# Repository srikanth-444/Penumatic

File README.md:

# _Peumatic Backpack_
This is a Penumatic System that senses and actuates the multiple soft actuators while communicating with the remote pc 

## _Hardware_ 
To control and sense the robotic actuator system, developed using KiCad 8, this repository will build the Gerber files of the system upon pushing the action artifacts specific to JLCPCB 

| Component     | Function            | Notes                                                    |
| ------------- | ------------------- | -------------------------------------------------------- |
| **ESP-32 S3** | Microcontroller     | Handles system control, communication, and overall logic |
| **LTC2498**   | 24-bit ADC          | Senses actuator position with high precision             |
| **LTC6906**   | External oscillator | Provides clock signal for ADC operation                  |
| **MCZ33996**  | Solenoid driver     | Actuates solenoidal valves based on control signals      |

## _Firmware_ 
Developed in C using FreeRTOS for increased concurrency. Code is developed using VSCode ESP-IDF extension

### Images

rendered with [kicad-render](https://github.com/linalinn/kicad-render)

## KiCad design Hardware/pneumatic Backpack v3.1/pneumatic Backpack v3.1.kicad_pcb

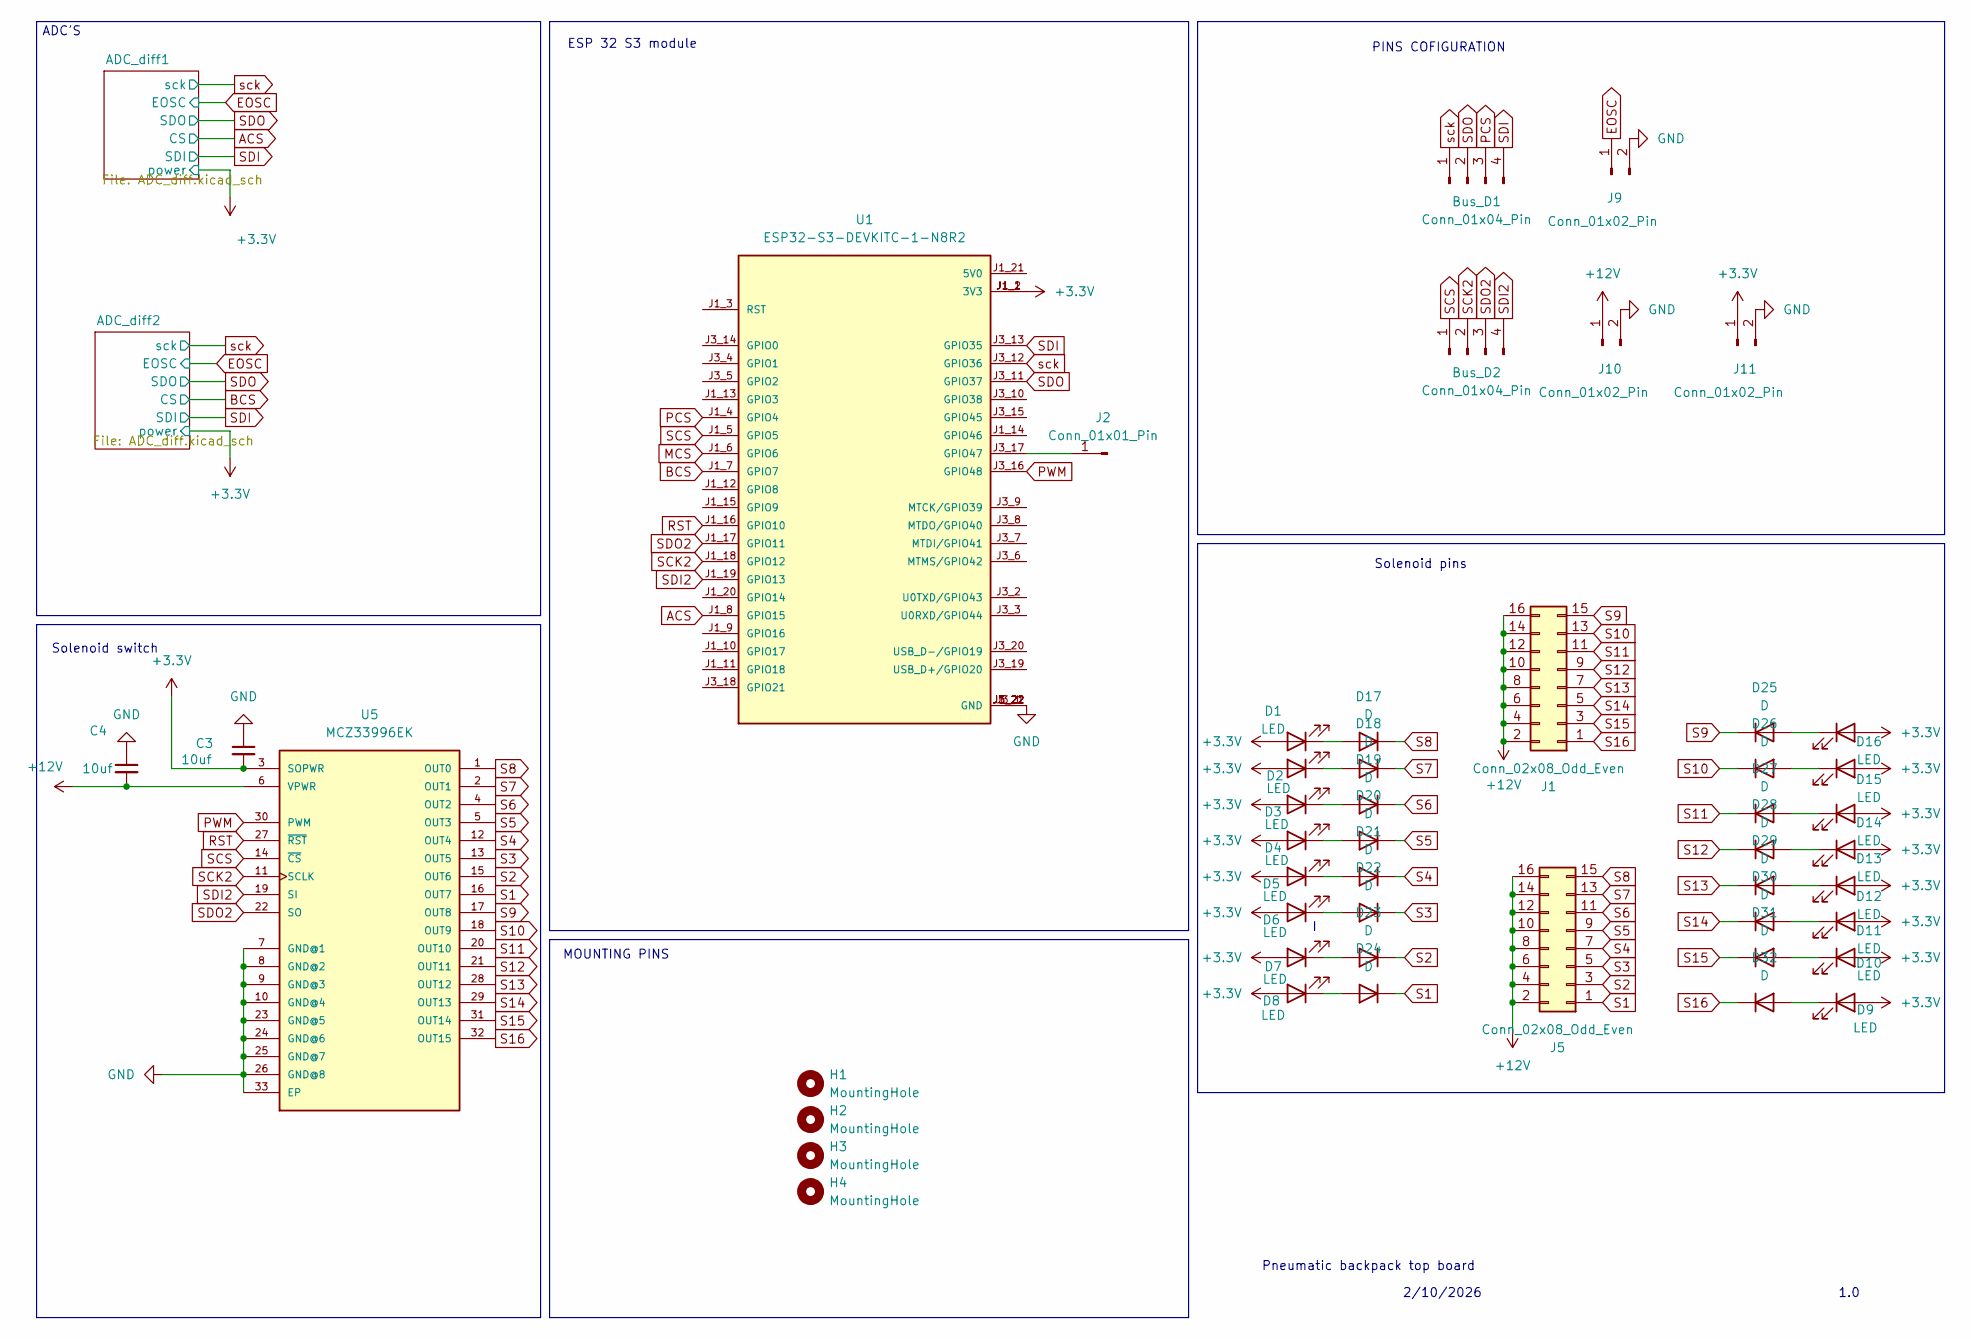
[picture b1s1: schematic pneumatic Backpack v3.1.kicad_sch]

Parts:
Bus_D1: Conn_01x04_Pin; PinSocket_1x04_P2.54mm_Vertical
Bus_D2: Conn_01x04_Pin; PinSocket_1x04_P2.54mm_Horizontal
C3, C4: 10uf; C_1206_3216Metric_Pad1.33x1.80mm_HandSolder
D1, D2, D3, D4, D5, D6, D7, D8, D9, D10, D11, D12, D13, D14, D15, D16: LED; LED_0805_2012Metric_Pad1.15x1.40mm_HandSolder
D17, D18, D19, D20, D21, D22, D23, D24, D25, D26, D27, D28, D29, D30, D31, D32: D; D_0805_2012Metric_Pad1.15x1.40mm_HandSolder
H1, H2, H3, H4: MountingHole; MountingHole_2.5mm
J1, J5: Conn_02x08_Odd_Even; JST_PHD_S16B-PHDSS_2x08_P2.00mm_Horizontal
J2: Conn_01x01_Pin; SolderWire-0.15sqmm_1x01_D0.5mm_OD1.5mm
J9, J10, J11: Conn_01x02_Pin; PinSocket_1x02_P2.54mm_Vertical
U1: ESP32-S3-DEVKITC-1-N8R2; XCVR_ESP32-S3-DEVKITC-1-N8R2; PARTREV V1
U5: MCZ33996EK; SOP65P1030X265-33N

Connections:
+3.3V: C3.2, D1.2 (A), D2.2 (A), D3.2 (A), D4.2 (A), D5.2 (A), D6.2 (A), D7.2 (A), D8.2 (A), D9.2 (A), D10.2 (A), D11.2 (A), D12.2 (A), D13.2 (A), D14.2 (A), D15.2 (A), D16.2 (A), J11.1, U1.J1_1 (3V3), U1.J1_2 (3V3), U5.3 (SOPWR); also elsewhere on the board
+12V: C4.2, J1.2, J1.4, J1.6, J1.8, J1.10, J1.12, J1.14, J1.16, J5.2, J5.4, J5.6, J5.8, J5.10, J5.12, J5.14, J5.16, J10.1, U5.6 (VPWR)
ACS: U1.J1_8 (GPIO15); also elsewhere on the board
BCS: U1.J1_7 (GPIO7); also elsewhere on the board
EOSC: J9.1; also elsewhere on the board
GND: C3.1, C4.1, J9.2, J10.2, J11.2, U1.J1_22 (GND), U1.J3_1 (GND), U1.J3_21 (GND), U1.J3_22 (GND), U5.7 (GND@1), U5.8 (GND@2), U5.9 (GND@3), U5.10 (GND@4), U5.23 (GND@5), U5.24 (GND@6), U5.25 (GND@7), U5.26 (GND@8), U5.33 (EP); also elsewhere on the board
MCS: U1.J1_6 (GPIO6)
unnamed: D1.1 (K), D17.2 (A)
unnamed: D10.1 (K), D31.2 (A)
unnamed: D11.1 (K), D30.2 (A)
unnamed: D12.1 (K), D29.2 (A)
unnamed: D13.1 (K), D28.2 (A)
unnamed: D14.1 (K), D27.2 (A)
unnamed: D15.1 (K), D26.2 (A)
unnamed: D16.1 (K), D25.2 (A)
unnamed: D2.1 (K), D18.2 (A)
unnamed: D3.1 (K), D19.2 (A)
unnamed: D4.1 (K), D20.2 (A)
unnamed: D5.1 (K), D21.2 (A)
unnamed: D6.1 (K), D22.2 (A)
unnamed: D7.1 (K), D23.2 (A)
unnamed: D8.1 (K), D24.2 (A)
unnamed: D9.1 (K), D32.2 (A)
unnamed: J2.1, U1.J3_17 (GPIO47)
PCS: Bus_D1.3, U1.J1_4 (GPIO4)
PWM: U1.J3_16 (GPIO48), U5.30 (PWM)
RST: U1.J1_16 (GPIO10), U5.27 (~RST)
S1: D24.1 (K), J5.1, U5.16 (OUT7)
S2: D23.1 (K), J5.3, U5.15 (OUT6)
S3: D22.1 (K), J5.5, U5.13 (OUT5)
S4: D21.1 (K), J5.7, U5.12 (OUT4)
S5: D20.1 (K), J5.9, U5.5 (OUT3)
S6: D19.1 (K), J5.11, U5.4 (OUT2)
S7: D18.1 (K), J5.13, U5.2 (OUT1)
S8: D17.1 (K), J5.15, U5.1 (OUT0)
S9: D25.1 (K), J1.15, U5.17 (OUT8)
S10: D26.1 (K), J1.13, U5.18 (OUT9)
S11: D27.1 (K), J1.11, U5.20 (OUT10)
S12: D28.1 (K), J1.9, U5.21 (OUT11)
S13: D29.1 (K), J1.7, U5.28 (OUT12)
S14: D30.1 (K), J1.5, U5.29 (OUT13)
S15: D31.1 (K), J1.3, U5.31 (OUT14)
S16: D32.1 (K), J1.1, U5.32 (OUT15)
SCK2: Bus_D2.2, U1.J1_18 (GPIO12), U5.11 (SCLK)
SCS: Bus_D2.1, U1.J1_5 (GPIO5), U5.14 (~CS)
SDI: Bus_D1.4, U1.J3_13 (GPIO35); also elsewhere on the board
SDI2: Bus_D2.4, U1.J1_19 (GPIO13), U5.19 (SI)
SDO: Bus_D1.2, U1.J3_11 (GPIO37); also elsewhere on the board
SDO2: Bus_D2.3, U1.J1_17 (GPIO11), U5.22 (SO)
sck: Bus_D1.1, U1.J3_12 (GPIO36); also elsewhere on the board

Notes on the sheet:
ADC'S
Solenoid pins
Solenoid switch
MOUNTING PINS
ESP 32 S3 module
Pneumatic backpack top board
1.0
2/10/2026
PINS COFIGURATION

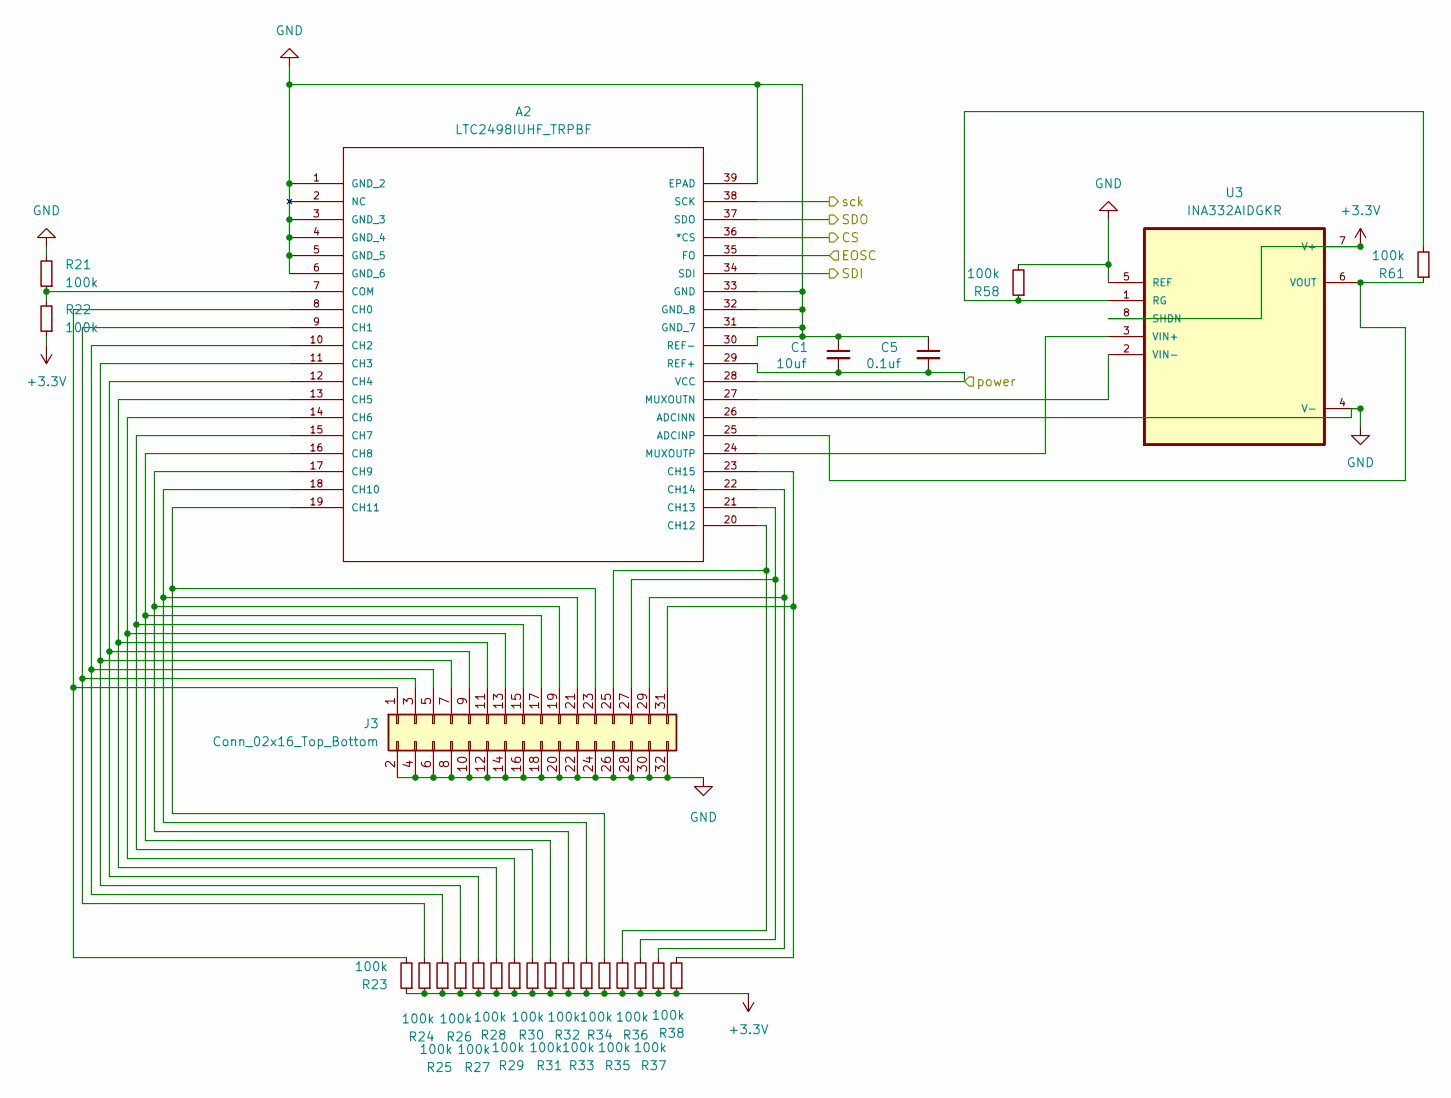
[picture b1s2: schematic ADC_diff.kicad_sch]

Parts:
A2: LTC2498IUHF_TRPBF; QFN-38_UHF; MANUFACTURER_PART_NUMBER ltc2498iuhf
C1: 10uf; C_1206_3216Metric_Pad1.33x1.80mm_HandSolder
C5: 0.1uf; C_1206_3216Metric_Pad1.33x1.80mm_HandSolder
J3: Conn_02x16_Top_Bottom; PinHeader_2x16_P2.54mm_Vertical
R21, R22, R23, R24, R25, R26, R27, R28, R29, R30, R31, R32, R33, R34, R35, R36, R37, R38, R58, R61: 100k; R_0805_2012Metric_Pad1.20x1.40mm_HandSolder
U3: INA332AIDGKR; SOP65P490X110-8N

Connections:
+3.3V: A2.28 (VCC), A2.29 (REF+), C1.2, C5.2, R22.1, R23.1, R24.1, R25.1, R26.1, R27.1, R28.1, R29.1, R30.1, R31.1, R32.1, R33.1, R34.1, R35.1, R36.1, R37.1, R38.1, U3.7 (V+), U3.8 (SHDN); also elsewhere on the board
ACS: A2.36 (*CS); also elsewhere on the board
EOSC: A2.35 (FO); also elsewhere on the board
GND: A2.1 (GND_2), A2.3 (GND_3), A2.4 (GND_4), A2.5 (GND_5), A2.6 (GND_6), A2.26 (ADCINN), A2.30 (REF-), A2.31 (GND_7), A2.32 (GND_8), A2.33 (GND), A2.39 (EPAD), C1.1, C5.1, J3.2, J3.4, J3.6, J3.8, J3.10, J3.12, J3.14, J3.16, J3.18, J3.20, J3.22, J3.24, J3.26, J3.28, J3.30, J3.32, R21.2, R58.2, U3.4 (V-), U3.5 (REF); also elsewhere on the board
unnamed: A2.25 (ADCINP), R61.1, U3.6 (VOUT)
unnamed: A2.8 (CH0), J3.1, R23.2
unnamed: A2.9 (CH1), J3.3, R24.2
unnamed: A2.10 (CH2), J3.5, R25.2
unnamed: A2.11 (CH3), J3.7, R26.2
unnamed: A2.12 (CH4), J3.9, R27.2
unnamed: A2.13 (CH5), J3.11, R28.2
unnamed: A2.14 (CH6), J3.13, R29.2
unnamed: A2.15 (CH7), J3.15, R30.2
unnamed: A2.16 (CH8), J3.17, R31.2
unnamed: A2.17 (CH9), J3.19, R32.2
unnamed: A2.18 (CH10), J3.21, R33.2
unnamed: A2.19 (CH11), J3.23, R34.2
unnamed: A2.20 (CH12), J3.25, R35.2
unnamed: A2.21 (CH13), J3.27, R36.2
unnamed: A2.22 (CH14), J3.29, R37.2
unnamed: A2.23 (CH15), J3.31, R38.2
unnamed: A2.7 (COM), R21.1, R22.2
unnamed: A2.27 (MUXOUTN), U3.2 (VIN-)
unnamed: A2.24 (MUXOUTP), U3.3 (VIN+)
unnamed: R58.1, R61.2, U3.1 (RG)
SDI: A2.34 (SDI); also elsewhere on the board
SDO: A2.37 (SDO); also elsewhere on the board
sck: A2.38 (SCK); also elsewhere on the board

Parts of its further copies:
A3: LTC2498IUHF_TRPBF; QFN-38_UHF; MANUFACTURER_PART_NUMBER ltc2498iuhf
C2: 10uf; C_1206_3216Metric_Pad1.33x1.80mm_HandSolder
C6: 0.1uf; C_1206_3216Metric_Pad1.33x1.80mm_HandSolder
J4: Conn_02x16_Top_Bottom; PinHeader_2x16_P2.54mm_Vertical
R39, R40, R41, R42, R43, R44, R45, R46, R47, R48, R49, R50, R51, R52, R53, R54, R55, R56, R59, R62: 100k; R_0805_2012Metric_Pad1.20x1.40mm_HandSolder
U4: INA332AIDGKR; SOP65P490X110-8N

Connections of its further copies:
+3.3V: A3.28 (VCC), A3.29 (REF+), C2.2, C6.2, R40.1, R41.1, R42.1, R43.1, R44.1, R45.1, R46.1, R47.1, R48.1, R49.1, R50.1, R51.1, R52.1, R53.1, R54.1, R55.1, R56.1, U4.7 (V+), U4.8 (SHDN); also elsewhere on the board
BCS: A3.36 (*CS); also elsewhere on the board
EOSC: A3.35 (FO); also elsewhere on the board
GND: A3.1 (GND_2), A3.3 (GND_3), A3.4 (GND_4), A3.5 (GND_5), A3.6 (GND_6), A3.26 (ADCINN), A3.30 (REF-), A3.31 (GND_7), A3.32 (GND_8), A3.33 (GND), A3.39 (EPAD), C2.1, C6.1, J4.2, J4.4, J4.6, J4.8, J4.10, J4.12, J4.14, J4.16, J4.18, J4.20, J4.22, J4.24, J4.26, J4.28, J4.30, J4.32, R39.2, R59.2, U4.4 (V-), U4.5 (REF); also elsewhere on the board
unnamed: A3.25 (ADCINP), R62.1, U4.6 (VOUT)
unnamed: A3.8 (CH0), J4.1, R41.2
unnamed: A3.9 (CH1), J4.3, R42.2
unnamed: A3.10 (CH2), J4.5, R43.2
unnamed: A3.11 (CH3), J4.7, R44.2
unnamed: A3.12 (CH4), J4.9, R45.2
unnamed: A3.13 (CH5), J4.11, R46.2
unnamed: A3.14 (CH6), J4.13, R47.2
unnamed: A3.15 (CH7), J4.15, R48.2
unnamed: A3.16 (CH8), J4.17, R49.2
unnamed: A3.17 (CH9), J4.19, R50.2
unnamed: A3.18 (CH10), J4.21, R51.2
unnamed: A3.19 (CH11), J4.23, R52.2
unnamed: A3.20 (CH12), J4.25, R53.2
unnamed: A3.21 (CH13), J4.27, R54.2
unnamed: A3.22 (CH14), J4.29, R55.2
unnamed: A3.23 (CH15), J4.31, R56.2
unnamed: A3.7 (COM), R39.1, R40.2
unnamed: A3.27 (MUXOUTN), U4.2 (VIN-)
unnamed: A3.24 (MUXOUTP), U4.3 (VIN+)
unnamed: R59.1, R62.2, U4.1 (RG)
SDI: A3.34 (SDI); also elsewhere on the board
SDO: A3.37 (SDO); also elsewhere on the board
sck: A3.38 (SCK); also elsewhere on the board

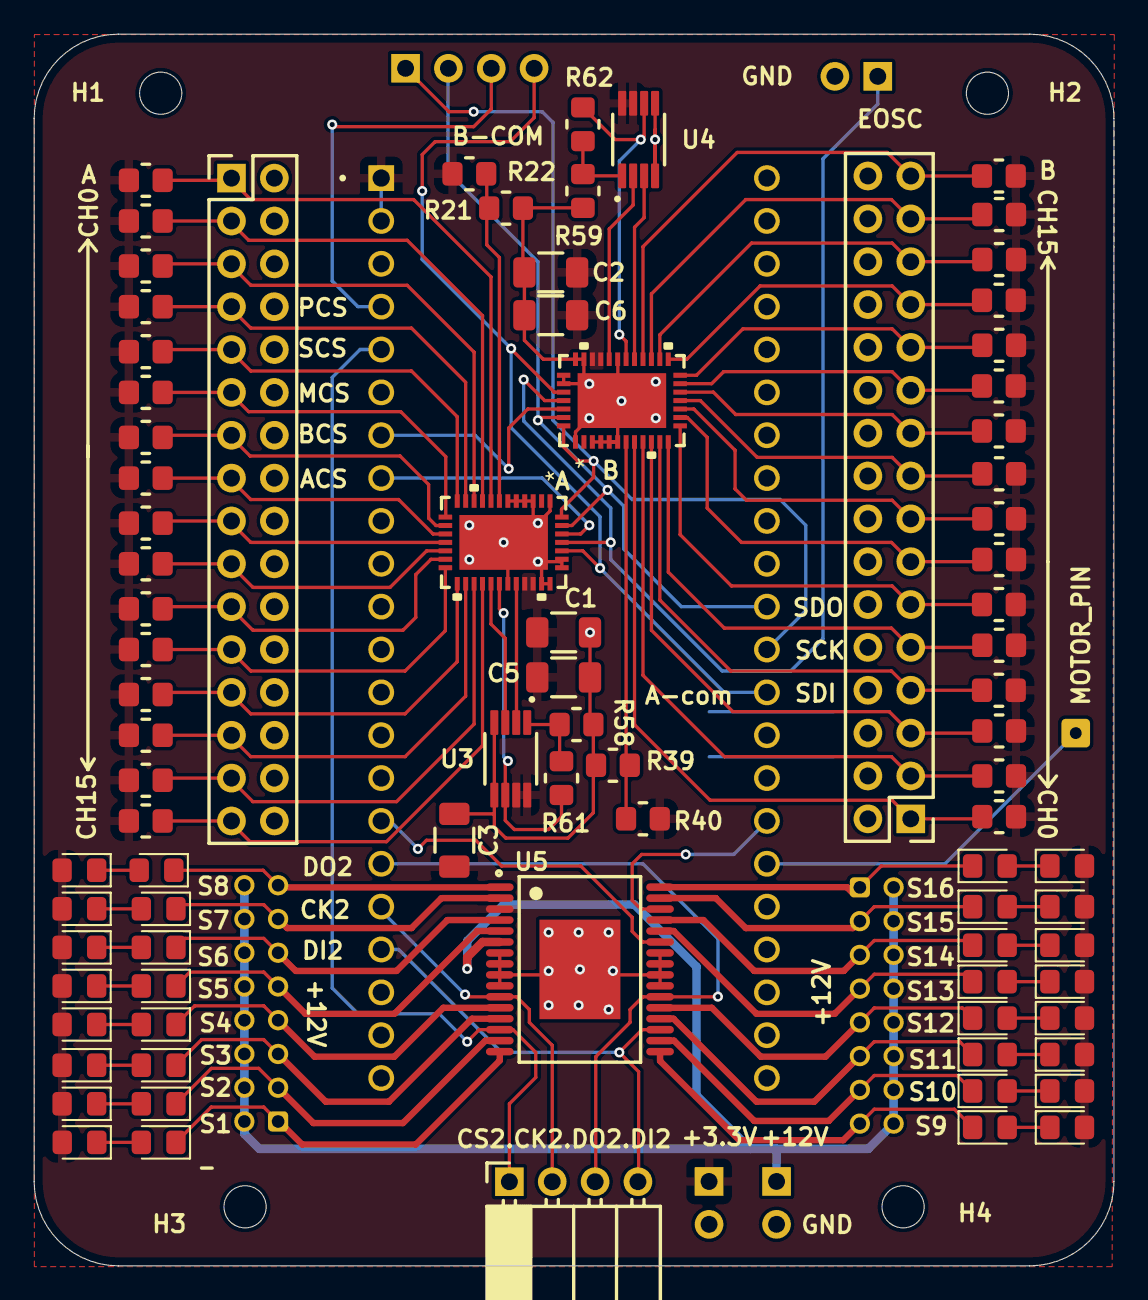
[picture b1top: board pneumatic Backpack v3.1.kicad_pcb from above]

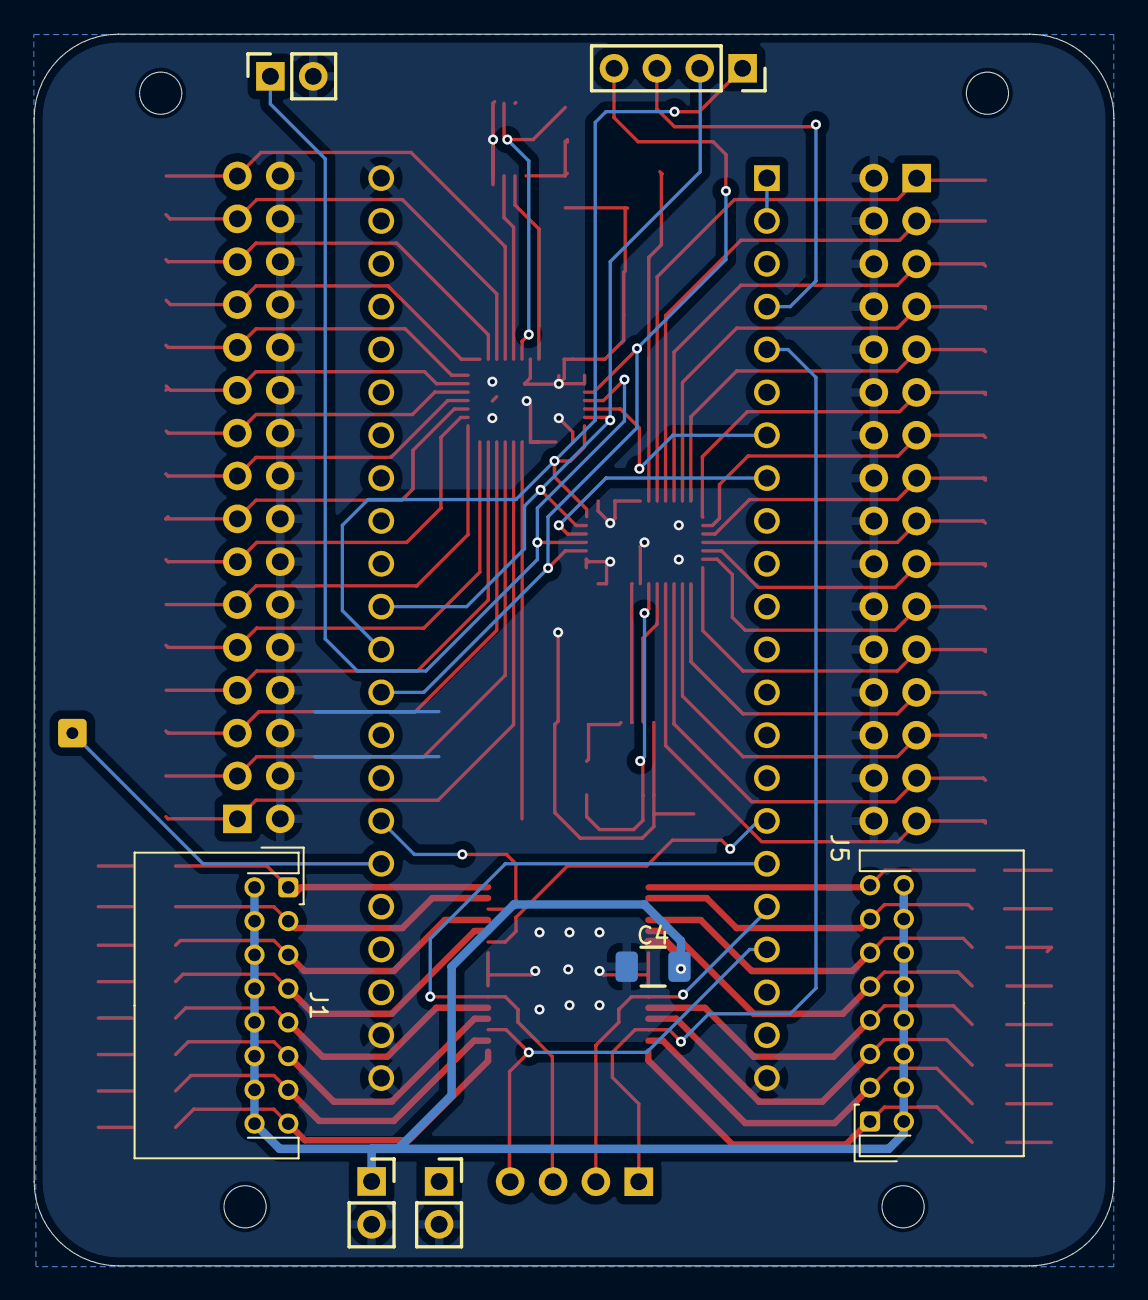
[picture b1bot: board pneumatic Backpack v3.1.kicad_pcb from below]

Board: 2 copper layers, 64.0 x 73.0 mm, 98 parts (7 on the bottom side), 91 nets.

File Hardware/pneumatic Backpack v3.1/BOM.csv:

"Reference","Value","Datasheet","Footprint","Qty","DNP"
"A2,A3","LTC2498IUHF_TRPBF","","mod:QFN-38_UHF","2",""
"Bus_D1,Bus_D2","Conn_01x04_Pin","~","-- mixed values --","2",""
"C1,C2,C3,C4","10uf","~","Capacitor_SMD:C_1206_3216Metric_Pad1.33x1.80mm_HandSolder","4",""
"C5,C6","0.1uf","~","Capacitor_SMD:C_1206_3216Metric_Pad1.33x1.80mm_HandSolder","2",""
"D1,D2,D3,D4,D5,D6,D7,D8,D9,D10,D11,D12,D13,D14,D15,D16","LED","~","LED_SMD:LED_0805_2012Metric_Pad1.15x1.40mm_HandSolder","16",""
"J1,J5","Conn_01x12_Pin","~","Connector_JST:JST_ZH_B12B-ZR_1x12_P1.50mm_Vertical","2",""
"J2","Conn_01x01_Pin","~","Connector_Wire:SolderWire-0.15sqmm_1x01_D0.5mm_OD1.5mm","1",""
"J3,J4","Conn_02x16_Top_Bottom","~","Connector_PinHeader_2.54mm:PinHeader_2x16_P2.54mm_Vertical","2",""
"J9,J10,J11","Conn_01x02_Pin","~","Connector_PinSocket_2.54mm:PinSocket_1x02_P2.54mm_Vertical","3",""
"R21,R22,R23,R24,R25,R26,R27,R28,R29,R30,R31,R32,R33,R34,R35,R36,R37,R38,R39,R40,R41,R42,R43,R44,R45,R46,R47,R48,R49,R50,R51,R52,R53,R54,R55,R56,R58,R59,R61,R62","100k","~","Resistor_SMD:R_0805_2012Metric_Pad1.20x1.40mm_HandSolder","40",""
"U1","ESP32-S3-DEVKITC-1-N8R2","","ESP32-S3-DEVKITC-1-N8R2:XCVR_ESP32-S3-DEVKITC-1-N8R2","1",""
"U3,U4","INA332AIDGKR","","INA332AIDGKR:SOP65P490X110-8N","2",""
"U5","MCZ33996EK","","MCZ33996EK:SOP65P1030X265-33N","1",""

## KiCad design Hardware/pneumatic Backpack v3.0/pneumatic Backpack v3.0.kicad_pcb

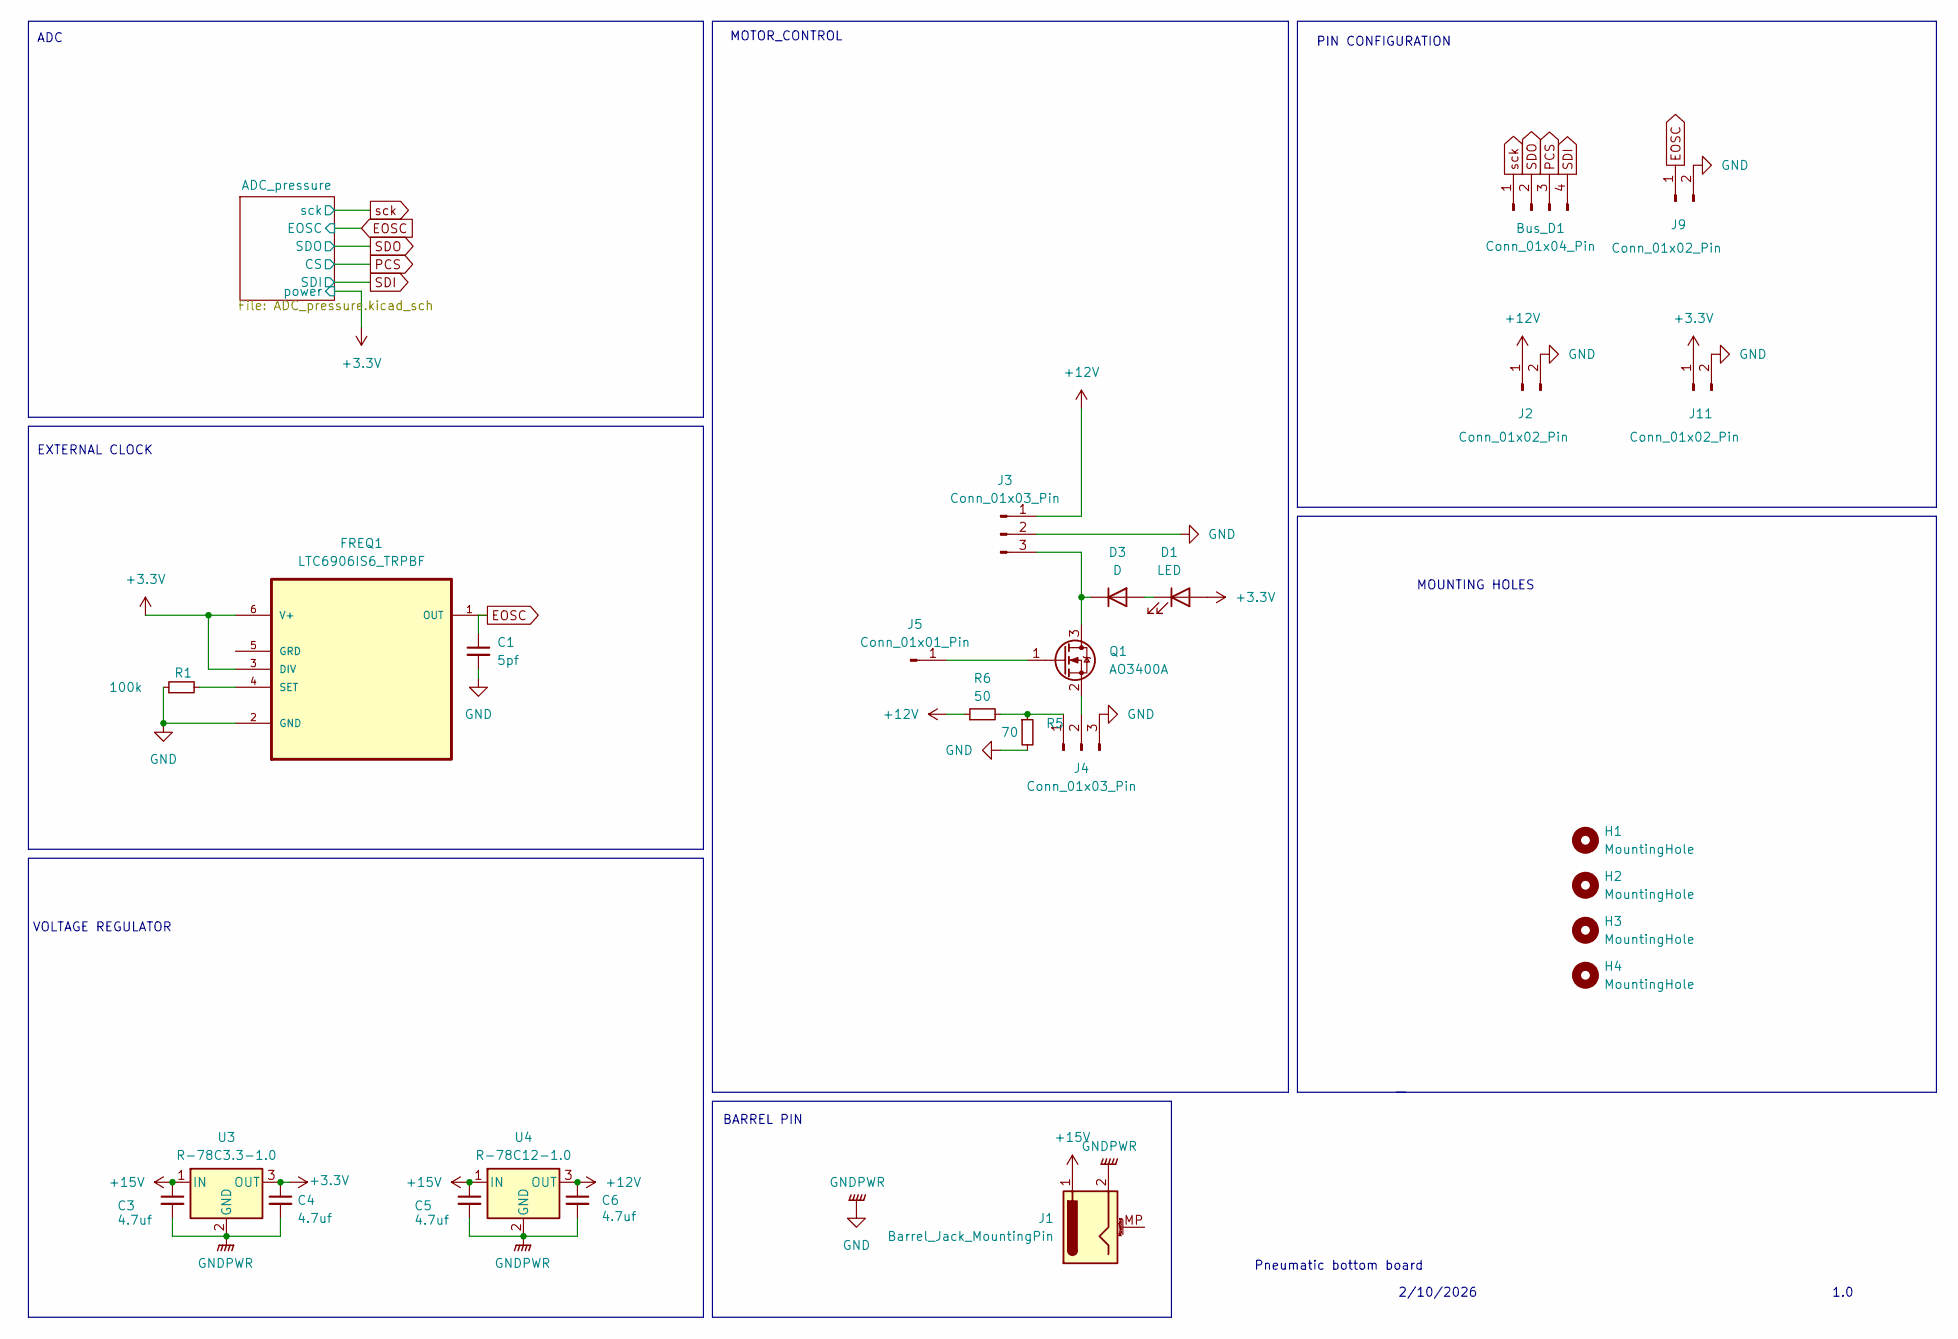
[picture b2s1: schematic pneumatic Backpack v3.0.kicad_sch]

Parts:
Bus_D1: Conn_01x04_Pin; PinSocket_1x04_P2.54mm_Vertical
C1: 5pf; C_1206_3216Metric_Pad1.33x1.80mm_HandSolder
C3, C4, C5, C6: 4.7uf; C_1206_3216Metric_Pad1.33x1.80mm_HandSolder
D1: LED; LED_0805_2012Metric_Pad1.15x1.40mm_HandSolder
D3: D; D_0805_2012Metric_Pad1.15x1.40mm_HandSolder
FREQ1: LTC6906IS6_TRPBF; SOT95P280X100-6N; MPN LTC6906IS6#PBF
H1, H2, H3, H4: MountingHole; MountingHole_2.5mm
J1: Barrel_Jack_MountingPin; BarrelJack_Horizontal
J2, J9, J11: Conn_01x02_Pin; PinSocket_1x02_P2.54mm_Vertical
J3: Conn_01x03_Pin; JST_ZH_B3B-ZR_1x03_P1.50mm_Vertical
J4: Conn_01x03_Pin; PinHeader_1x03_P2.54mm_Vertical
J5: Conn_01x01_Pin; SolderWire-0.15sqmm_1x01_D0.5mm_OD1.5mm
Q1: AO3400A; SOT-23
R1: 100k; R_0805_2012Metric_Pad1.20x1.40mm_HandSolder
R5: 70; R_0805_2012Metric_Pad1.20x1.40mm_HandSolder
R6: 50; R_0805_2012Metric_Pad1.20x1.40mm_HandSolder
U3: R-78C3.3-1.0; Converter_DCDC_RECOM_R-78E-0.5_THT
U4: R-78C12-1.0; Converter_DCDC_RECOM_R-78E-0.5_THT

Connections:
+3.3V: C4.1, D1.2 (A), FREQ1.3 (DIV), FREQ1.6 (V+), J11.1, U3.3 (OUT); also elsewhere on the board
+12V: C6.1, J2.1, J3.1, R6.1, U4.3 (OUT)
+15V: C3.1, C5.1, J1.1, U3.1 (IN), U4.1 (IN)
EOSC: C1.1, FREQ1.1 (OUT), J9.1; also elsewhere on the board
GND: C1.2, C3.2, C4.2, C5.2, C6.2, FREQ1.2 (GND), J1.2, J2.2, J3.2, J4.3, J9.2, J11.2, R1.1, R5.2, U3.2 (GND), U4.2 (GND); also elsewhere on the board
unnamed: D1.1 (K), D3.2 (A)
unnamed: D3.1 (K), J3.3, Q1.3 (D)
unnamed: FREQ1.4 (SET), R1.2
unnamed: J4.1, R5.1, R6.2
unnamed: J4.2, Q1.2 (S)
unnamed: J5.1, Q1.1 (G)
PCS: Bus_D1.3; also elsewhere on the board
SDI: Bus_D1.4; also elsewhere on the board
SDO: Bus_D1.2; also elsewhere on the board
sck: Bus_D1.1; also elsewhere on the board

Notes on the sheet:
VOLTAGE REGULATOR
BARREL PIN
2/10/2026
MOUNTING HOLES
Pneumatic bottom board
1.0
PIN CONFIGURATION
MOTOR_CONTROL
ADC
EXTERNAL CLOCK

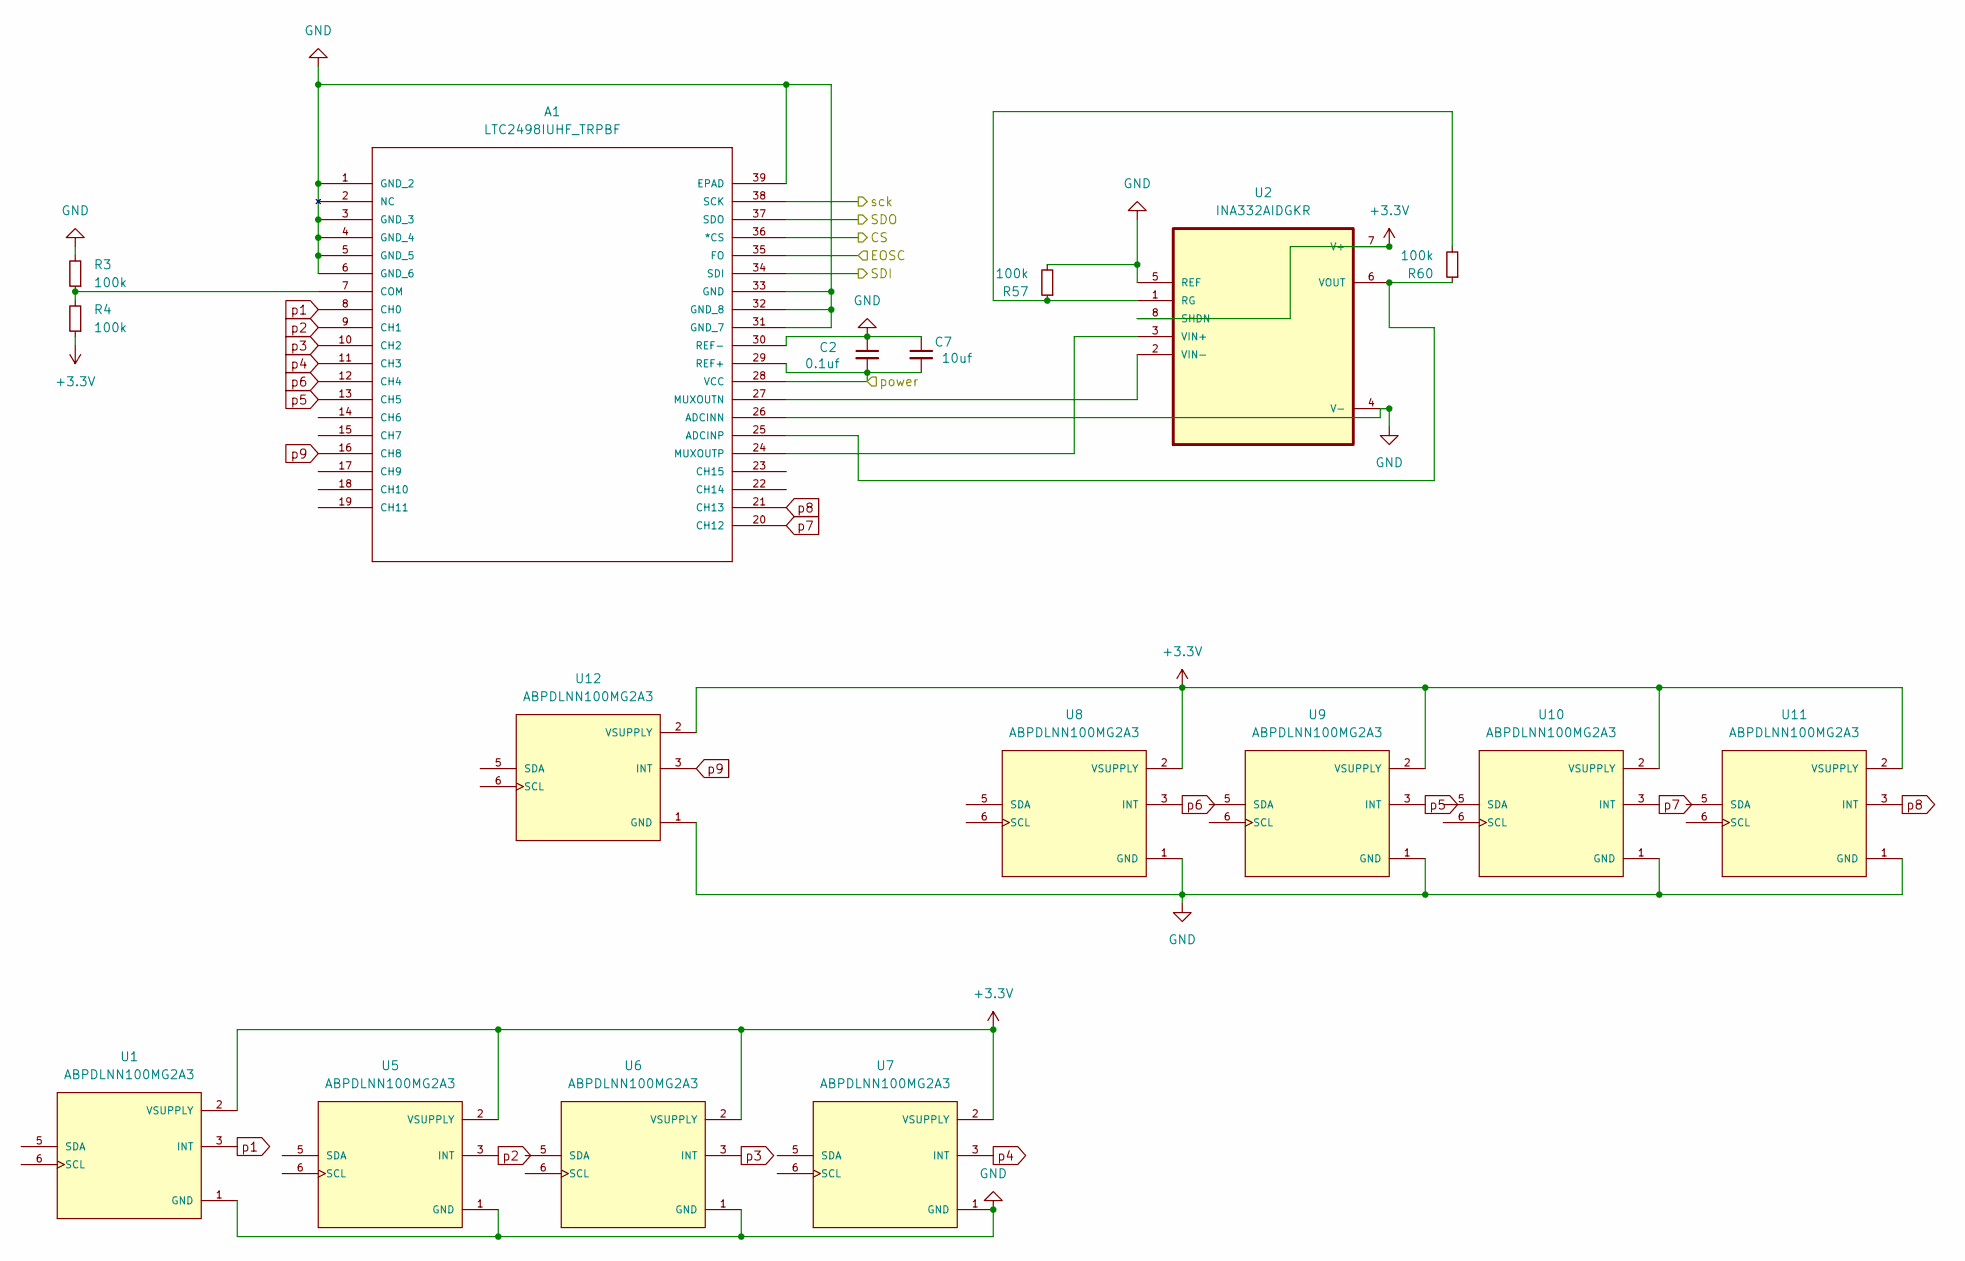
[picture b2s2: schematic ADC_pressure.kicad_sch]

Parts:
A1: LTC2498IUHF_TRPBF; QFN-38_UHF; MANUFACTURER_PART_NUMBER ltc2498iuhf
C2: 0.1uf; C_1206_3216Metric_Pad1.33x1.80mm_HandSolder
C7: 10uf; C_1206_3216Metric_Pad1.33x1.80mm_HandSolder
R3, R4, R57, R60: 100k; R_0805_2012Metric_Pad1.20x1.40mm_HandSolder
U1, U5, U6, U7, U8, U9, U10, U11, U12: ABPDLNN100MG2A3; XDCR_ABPDLNN100MG2A3; PARTREV E
U2: INA332AIDGKR; SOP65P490X110-8N

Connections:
+3.3V: A1.28 (VCC), A1.29 (REF+), C2.2, C7.2, R4.1, U1.2 (VSUPPLY), U2.7 (V+), U2.8 (SHDN), U5.2 (VSUPPLY), U6.2 (VSUPPLY), U7.2 (VSUPPLY), U8.2 (VSUPPLY), U9.2 (VSUPPLY), U10.2 (VSUPPLY), U11.2 (VSUPPLY), U12.2 (VSUPPLY); also elsewhere on the board
EOSC: A1.35 (FO); also elsewhere on the board
GND: A1.1 (GND_2), A1.3 (GND_3), A1.4 (GND_4), A1.5 (GND_5), A1.6 (GND_6), A1.26 (ADCINN), A1.30 (REF-), A1.31 (GND_7), A1.32 (GND_8), A1.33 (GND), A1.39 (EPAD), C2.1, C7.1, R3.2, R57.2, U1.1 (GND), U2.4 (V-), U2.5 (REF), U5.1 (GND), U6.1 (GND), U7.1 (GND), U8.1 (GND), U9.1 (GND), U10.1 (GND), U11.1 (GND), U12.1 (GND); also elsewhere on the board
unnamed: A1.25 (ADCINP), R60.1, U2.6 (VOUT)
unnamed: A1.7 (COM), R3.1, R4.2
unnamed: A1.27 (MUXOUTN), U2.2 (VIN-)
unnamed: A1.24 (MUXOUTP), U2.3 (VIN+)
unnamed: R57.1, R60.2, U2.1 (RG)
PCS: A1.36 (*CS); also elsewhere on the board
SDI: A1.34 (SDI); also elsewhere on the board
SDO: A1.37 (SDO); also elsewhere on the board
p1: A1.8 (CH0), U1.3 (INT)
p2: A1.9 (CH1), U5.3 (INT)
p3: A1.10 (CH2), U6.3 (INT)
p4: A1.11 (CH3), U7.3 (INT)
p5: A1.13 (CH5), U9.3 (INT)
p6: A1.12 (CH4), U8.3 (INT)
p7: A1.20 (CH12), U10.3 (INT)
p8: A1.21 (CH13), U11.3 (INT)
p9: A1.16 (CH8), U12.3 (INT)
sck: A1.38 (SCK); also elsewhere on the board
